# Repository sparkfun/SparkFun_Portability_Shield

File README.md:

SparkFun Portability Shield
========================================

[*SparkFun Portability Shield (DEV-27510)*](https://www.sparkfun.com/products/27510)

The SparkFun Portability Shield adds all the user interface bits needed to take a SparkFun development board into the field. A LiPo battery connector, charger, fuel gauge, and an on/off switch address your power needs. A friction-fit microSD connector allows for data logging. The 1.3in. OLED and a five-way navigation switch provide an excellent user interface. Locking 0.1in. headers along the shield's edge make it easier to solder male pins in place.

I<sup>2</sup>C is used to interface with the display, fuel gauge, and five-way navigation switch (GPIO expander PCA9554). SPI is used to communicate with the microSD card. The power switch uses an ideal diode (LM66200) to disconnect the battery from the system for a sleep current of approximately 4μA.

The Portability Shield has been designed to be usable with any compatible main board, with the [RTK Postcard](https://www.sparkfun.com/products/26916) being the first!

Head to the [Sparkfun Portability Shield Product Manual](http://docs.sparkfun.com/SparkFun_Portability_Shield/) for technical documentation.

Repository Contents
-------------------

* **/Hardware** - KiCad design files (.kicad_pro, .kicad_pcb, kicad_sch)
* **/docs** - Documentation for the github pages version of this hookup guide

License Information
-------------------

This product is _**open source**_!

Please review the LICENSE.md file for license information.

If you have any questions or concerns on licensing, please contact technical support on our [SparkFun forums](https://forum.sparkfun.com/viewforum.php?f=152).

Distributed as-is; no warranty is given.

- Your friends at SparkFun.

_<COLLABORATION CREDIT>_

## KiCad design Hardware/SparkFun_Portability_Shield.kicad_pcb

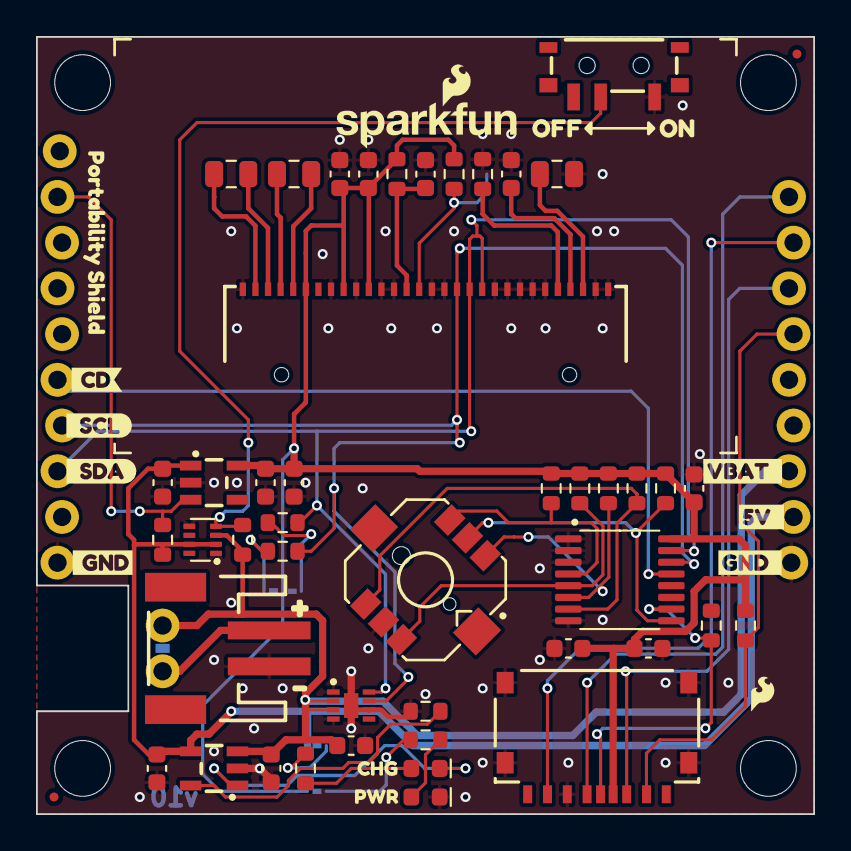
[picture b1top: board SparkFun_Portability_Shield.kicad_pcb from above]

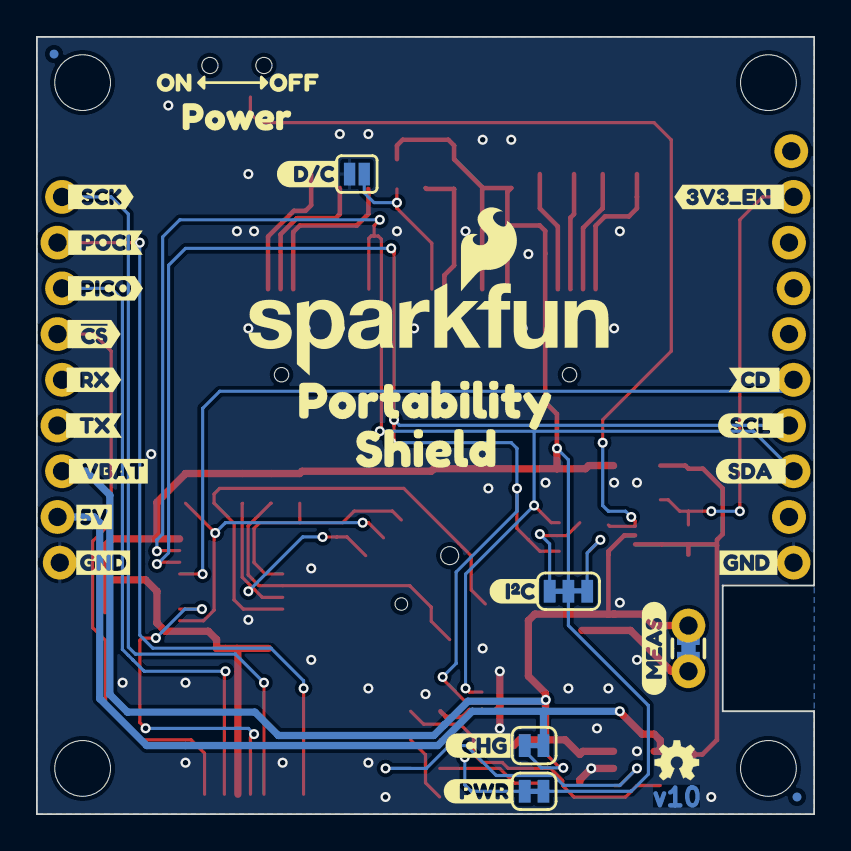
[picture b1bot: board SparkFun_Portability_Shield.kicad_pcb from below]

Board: 2 copper layers, 43.2 x 43.2 mm, 100 parts (32 on the bottom side), 37 nets.

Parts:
C1, C10: 10uF; C_0603_1608Metric
C2, C3, C9, C13, C16: 0.1uF; C_0603_1608Metric
C4, C5, C12: 4.7uF; C_0603_1608Metric
C6, C7, C8: 1.0uF; C_0603_1608Metric
C11, C14: 1.0uF; C_0805_2012Metric
C15: 2.2uF; C_0805_2012Metric
D1: Yellow; LED_0603_1608Metric_Yellow
D3: Red; LED_0603_1608Metric_Red
FID1, FID2, FID3, FID4: Fiducial_0.5mm; Fiducial_0.5mm_Mask1mm
G1: OSHW_Logo; Creative_Commons_License
J1: microSD_Friction; microSD_Friction_Fit_Common
J2: 1x10; 1x10_Locking
J3: JST_2mm_LiPo; JST_SMD_2.0mm-2
J4: 1x09; 1x09_Locking
JP1: CHG; Jumper_2_NC_Trace
JP2: D/C; Jumper_2_NO
JP3: PWR; Jumper_2_NC_Trace
JP4: I²C; Jumper_3_NC-2_Trace
JP5: MEAS; Jumper_2_PTH_SMD_Combo-NC
R1, R2, R5, R6, R8, R9, R10, R11, R12: 10k; R_0603_1608Metric
R3: 2.0k; R_0603_1608Metric
R4, R14: 1k; R_0603_1608Metric
R7: 390k; R_0603_1608Metric
R13, R17: 100k; R_0603_1608Metric
R15, R16: 2.2k; R_0603_1608Metric
Ref**: Val**; OSHW_Logo_2.5mm
ST1, ST2, ST3, ST4: Standoff
SW1: SPDT_Slide_SMD_6.7x2.6mm; Slide_SPST_SMD_6.7x2.6mm
SW2: Nav Switch; Navigation_SMD_7.5x7.5mm
U1: AP2112K-3.3; SOT23-5
U2: MAX17048; DFN-8
U3: MCP73831; SOT23-5
U4: PCA9554PW; TSSOP-16_4.4x5mm_P0.65mm
U5: OLED_1.3"; OLED-1.3-128X64-Folded
U7: LM66200; SOT-583-8
kibuzzard-66CAA9A5: G***; kibuzzard-66CAA9A5
kibuzzard-66CB37A9: G***; kibuzzard-66CB37A9
kibuzzard-66F0B700: G***; kibuzzard-66F0B700
kibuzzard-66F0B716: G***; kibuzzard-66F0B716
kibuzzard-66F0B764: G***; kibuzzard-66F0B764
kibuzzard-66F4A59B: G***; kibuzzard-66F4A59B
kibuzzard-66F4A593: G***; kibuzzard-66F4A593
kibuzzard-66F080CC: G***; kibuzzard-66F080CC
kibuzzard-66F080D6: G***; kibuzzard-66F080D6
kibuzzard-66F080E9: G***; kibuzzard-66F080E9
kibuzzard-66F080F8: G***; kibuzzard-66F080F8
kibuzzard-66F083A9: G***; kibuzzard-66F083A9
kibuzzard-66F083B5: G***; kibuzzard-66F083B5
kibuzzard-66F083BA: G***; kibuzzard-66F083BA
kibuzzard-66F085B1: G***; kibuzzard-66F085B1
kibuzzard-66F0824D: G***; kibuzzard-66F0824D
kibuzzard-66F0833D: G***; kibuzzard-66F0833D
kibuzzard-66F0844F: G***; kibuzzard-66F0844F
kibuzzard-66F0853A: G***; kibuzzard-66F0853A
kibuzzard-66F08248: G***; kibuzzard-66F08248
kibuzzard-66F08337: G***; kibuzzard-66F08337
kibuzzard-66F08463: G***; kibuzzard-66F08463
kibuzzard-66F08559: G***; kibuzzard-66F08559
kibuzzard-66F08561: G***; kibuzzard-66F08561
kibuzzard-66F08589: G***; kibuzzard-66F08589
kibuzzard-66F08591: G***; kibuzzard-66F08591
kibuzzard-66F08598: G***; kibuzzard-66F08598
kibuzzard-66F37954: G***; kibuzzard-66F37954
kibuzzard-673B98BA: G***; kibuzzard-673B98BA
kibuzzard-673B999B: G***; kibuzzard-673B999B
kibuzzard-673B9939: G***; kibuzzard-673B9939
kibuzzard-673B9961: G***; kibuzzard-673B9961
kibuzzard-673B9979: G***; kibuzzard-673B9979
kibuzzard-67140B1C, kibuzzard-67140B1C#2: G***; kibuzzard-67140B1C
kibuzzard-67140B31, kibuzzard-67140B31#2: G***; kibuzzard-67140B31
kibuzzard-67140CF9: G***; kibuzzard-67140CF9

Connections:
3.3V_P: C1.1, C2.1, C7.1, C8.1, C10.1, C13.1, C16.1, J1.4 (VDD), JP3.2 (B), JP4.2 (C), R1.2, R2.1, R5.1, R8.2, R9.2, R10.2, R11.2, R12.2, U1.5 (VOUT), U4.16 (VDD), U5.6 (VDDB), U5.9 (VDD), U5.11 (BS1)
3V3_EN: J2.2, R13.2, U1.3 (EN)
5V: C5.1, C9.1, J4.2, JP1.2 (B), R13.1, U1.1 (VIN), U3.4 (VIN), U7.2 (VOUT), U7.7 (VOUT)
GND: C1.2, C2.2, C3.2, C4.2, C5.2, C6.2, C7.2, C8.2, C9.2, C10.2, C12.2, C13.2, C15.2, C16.2, D3.1 (K), J1.6 (VSS), J1.10 (SHIELD), J2.10, J3.1 (-), J4.1, JP2.1 (A), R3.2, R6.2, R7.2, SW1.3 (C), SW2.2 (GND), U1.2 (GND), U2.1 (CTG), U2.4 (GND), U2.6 (QSTRT), U2.9 (GND), U3.2 (GND), U4.1 (A0), U4.2 (A1), U4.3 (A2), U4.8 (VSS), U5.1 (GND), U5.8 (VSS), U5.10 (BS0), U5.12 (BS2), U5.13 (~CS), U5.16 (R/~W), U5.17 (E/~RD), U5.21 (D3), U5.22 (D4), U5.23 (D5), U5.24 (D6), U5.25 (D7), U5.29 (VLSS), U5.30 (GND), U7.1 (GND), U7.5 (GND)
GPIO_~INT: J2.6, U4.13 (~INT)
unnamed: D1.2 (A), R4.1
unnamed: D1.1 (K), U3.1 (STAT)
unnamed: D3.2 (A), R14.2
unnamed: J3.2 (+), JP5.1 (A)
unnamed: JP1.1 (A), R4.2
unnamed: JP2.2 (B), R2.2, U5.15 (D/~C)
unnamed: JP3.1 (A), R14.1
unnamed: JP4.1 (A), R16.1
unnamed: JP4.3 (B), R15.1
unnamed: R3.1, U3.5 (PROG)
unnamed: C11.2, U5.5 (C1N)
unnamed: C11.1, U5.4 (C1P)
unnamed: C14.2, U5.3 (C2N)
unnamed: C14.1, U5.2 (C2P)
unnamed: R7.1, U5.26 (IREF)
unnamed: C15.1, U5.28 (VCC)
unnamed: C12.1, U5.27 (VCOMH)
unnamed: R17.2, SW1.2, U7.4 (~ON)
OLED_~RESET: C6.1, R1.1, U5.14 (~RESET)
SCL: J2.7, R15.2, U2.7 (SCL), U4.14 (SCL), U5.18 (D0/SCK/SCL)
SDA: J2.8, R16.2, U2.8 (SDA), U4.15 (SDA), U5.19 (D1/MOSI/SDA), U5.20 (D2/SDA)
SD_CD: J1.9 (DET), R6.1, U4.10 (IO5)
SHLD_PICO: J1.3 (CMD/SDI), J4.7
SHLD_POCI: J1.7 (DAT0/SDO), J4.8
SHLD_SCK: J1.5 (CLK/SCK), J4.9
SHLD_~CS: J1.2 (DAT3/~CS), J4.6, R5.2
SW_Center: R12.1, SW2.5 (Center), U4.9 (IO4)
SW_Down: R8.1, SW2.3 (Down), U4.5 (IO1)
SW_Left: R11.1, SW2.1 (Left), U4.7 (IO3)
SW_Right: R10.1, SW2.4 (Right), U4.6 (IO2)
SW_Up: R9.1, SW2.6 (Up), U4.4 (IO0)
VBATT: C3.1, C4.1, J4.3, JP5.2 (B), R17.1, U2.2 (CELL), U2.3 (VDD), U3.3 (V_{BAT}), U7.3 (VIN1)

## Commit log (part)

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2024-09-23 Add ignore.
2024-09-25 Change to dedicated header format.
2024-09-25 File rename.
2024-09-25 Route board
2024-09-25 File rename
2024-11-19 Fix nav switch. Adjust silk. Update to v10.
2024-11-20 Bones of the documentation
    Initial pass to get the framework in place
2024-11-21 Update I2C address on PCA9554
2024-11-22 Updating images and hardware overview
2024-11-22 Updating hardware overview and intro image
2024-11-22 Update README.md
    Adding image to ReadMe
2024-11-22 Finishing first pass of hardware overview
2024-11-25 Adding example sketches
2024-11-25 Adding example base and expanding intro a bit more
2024-11-25 Updates per Nate
2024-11-26 Updates to examples and link fixes
2024-11-26 Fixing resources link and including datasheets
2024-11-26 Adding Nate's description
2024-11-26 Argh formatting spaces
2024-11-26 Fixing single page and hard copy pages
2024-11-26 Fix preview image for RTK Product Manual
    Default images for these were the same - changing to be more appropriate
2024-11-27 Deployed 5a6e0ed with MkDocs version: 1.6.1
2024-12-05 Add link to library
2024-12-05 Fix ex 4 to work with latest SdFat library version
2024-12-05 Deployed 2388aa2 with MkDocs version: 1.6.1
2024-12-10 Adding examples and fixing missing admonition
2024-12-10 Update OLED model
2024-12-10 Add LM66200 battery switch
2024-12-11 Updated Action Shot with correct postcard
2024-12-11 Deployed fd3218c with MkDocs version: 1.6.1
2024-12-17 Update pin numbers to match production hardware
2024-12-18 Add 3D files
2024-12-18 Add 3D file for shield
2024-12-18 Deployed d40c326 with MkDocs version: 1.6.1
2025-01-07 Create thumbnail.jpg
    Add thumbnail to link tutorial with
2025-01-16 Update directional pad FP
2025-01-16 Deployed 9312c3c with MkDocs version: 1.6.1
2025-02-12 Fix link to product manual
2025-02-20 Adding fav logo
2025-02-20 Fixing fav logo
2025-02-20 Deployed 3d7a683 with MkDocs version: 1.6.1
2026-02-16 Added .step files for printing a thicker enclosure
    Notes: Thicker Housing Enclosures for the SparkFun RTK Postcard and Portability Shield combination
    There are two .step files (depending on how you connect the two modules):
    -------------------------
    Housing 2 v10 cc1-3.3mm.step (extra 3.3mm thick)
    - if soldering the two boards together with a set of male headers with just enough gap for a battery
    - the minimal thickness is a nice feature
2026-02-24 Fix documentation build
    Update parameters for webpage build and deployment
2026-02-24 Deployed cb770bf with MkDocs version: 1.6.1
2026-02-24 Update Docs
    - Removed extra spaces from end of lines
    - Add languages highlights to code blocks
    - Remove links to technical assistance page
    - Added related products
    - Updated page styling for build
2026-02-24 Deployed 4284d15 with MkDocs version: 1.6.1
2026-06-03 Deployed 83a5d89 with MkDocs version: 1.6.1

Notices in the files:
parts and their libraries:
https://creativecommons.org/licenses/by-sa/4.0
Released under the Creative Commons Attribution Share-Alike 4.0 License
